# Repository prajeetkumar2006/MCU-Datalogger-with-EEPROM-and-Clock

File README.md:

# MCU-Datalogger-with-EEPROM-and-Clock
A custom-designed ATmega328P-based data logger PCB featuring dual I²C EEPROMs and a DS1337 real-time clock for reliable time-stamped data storage.

This project is a microcontroller-based data logger designed using KiCad. It uses an ATmega328P as the main controller, a DS1337 real-time clock for accurate timekeeping, and dual 24LC1025 EEPROMs for non-volatile data storage. The system logs sensor or system data with date and time information and provides I²C, UART, and ICSP interfaces for communication, programming, and debugging.

# Features
- Microcontroller: ATmega328P-AU (16 MHz)
- Real-time clock: DS1337S with 32.768 kHz crystal
- Non-volatile memory: 2 × 24LC1025 EEPROM (I²C)
- Connectivity: I²C header, UART (RX/TX) header, GPIO header, 6-pin ICSP
- Indicators: 2 status LEDs
- Power: Coin-cell Battery (BT1) for RTC backup
- Board: 2-layer PCB; 87.63 mm × 39.116 mm; 4 mounting holes
- KiCad version: 9.0.0

## Hardware Components

### Integrated Circuits (ICs)
- ATmega328P – Main microcontroller
- DS1337 – Real-Time Clock (RTC)
- 24LC1025 – I2C EEPROM (x2)

### Resistors (R)
- R1 – 330 Ω
- R2, R3 – 4.7 kΩ
- R4 – 10 kΩ

### Capacitors (C)
- C1, C2 – 22 pF
- C3, C4 – 100 nF
- C5 – 10 µF

### Crystals (X)
- X1 – 16 MHz
- X2 – 32.768 kHz

### Connectors / Jumpers (J)
- ICSP header – MCU programming
- UART header – Serial communication
- I2C header – External peripherals
- Power header – VCC and GND

## Schematic Design

## PCB Design
### 2-Layer

### 4-Layer Design

## 3-D Model(2 Layer)

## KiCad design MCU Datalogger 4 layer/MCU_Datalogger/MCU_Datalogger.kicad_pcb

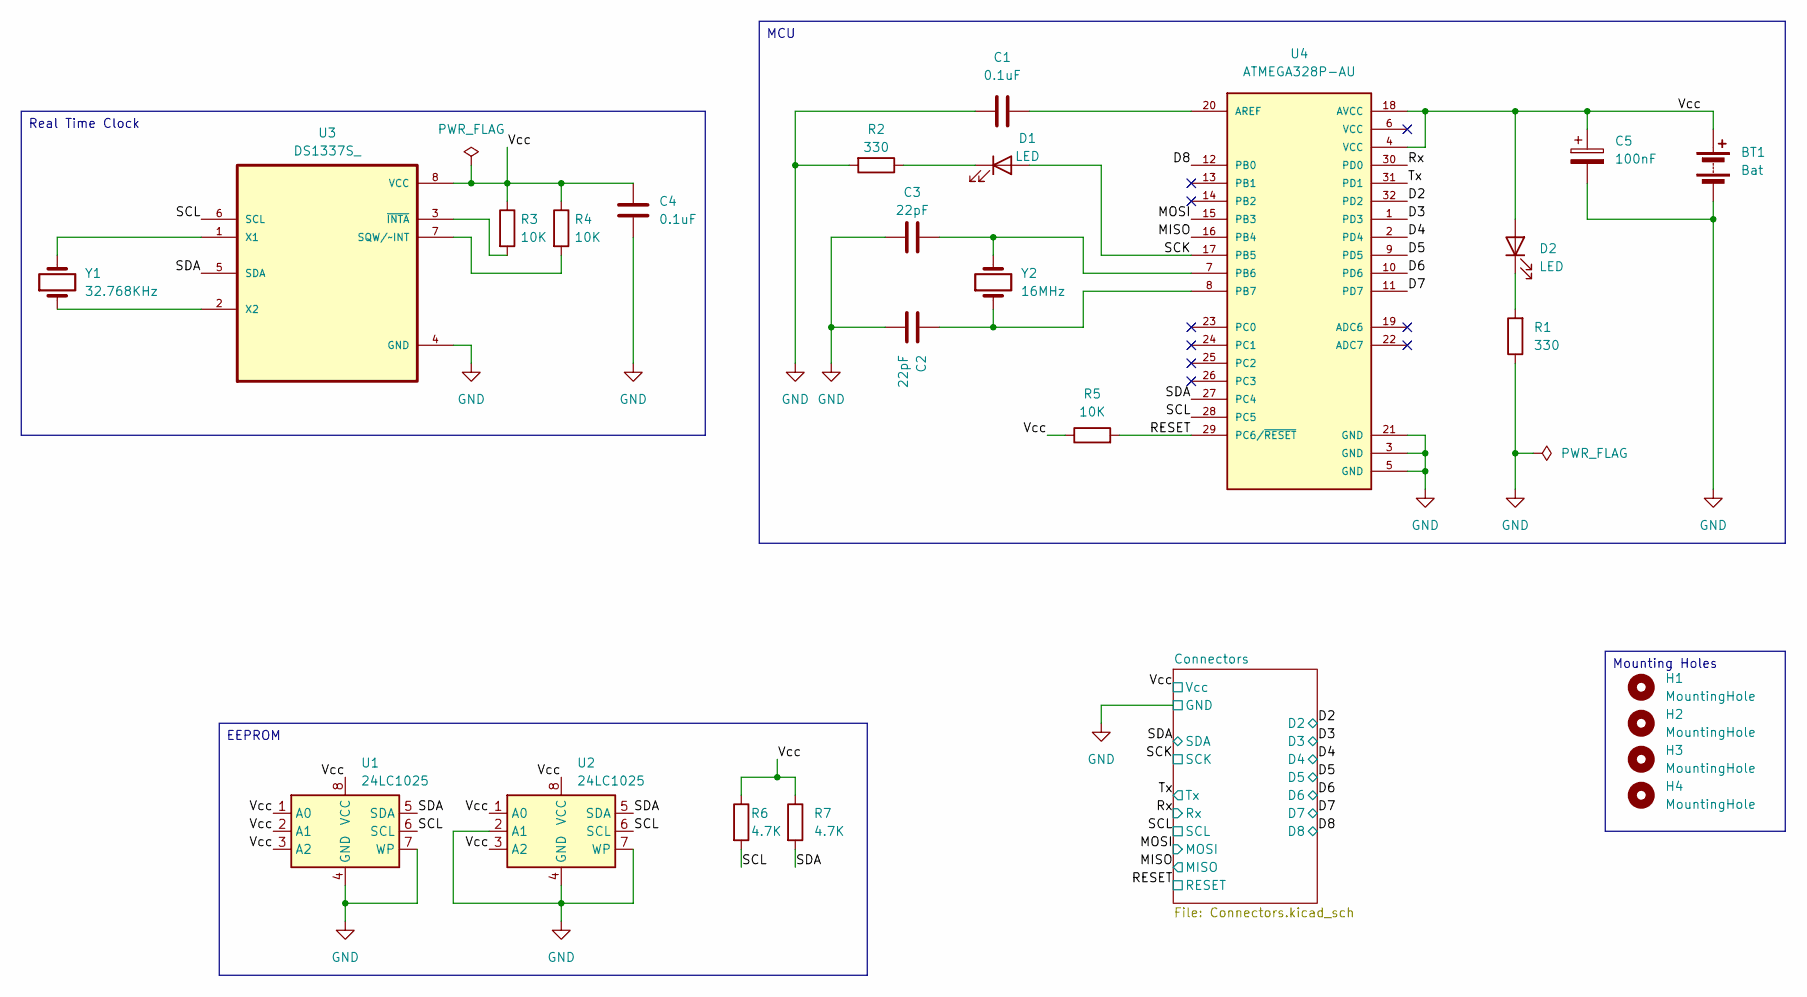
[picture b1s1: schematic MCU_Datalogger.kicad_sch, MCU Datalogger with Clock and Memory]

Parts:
BT1: Bat; PinHeader_1x02_P2.54mm_Vertical
C1, C4: 0.1uF; C_0805_2012Metric
C2, C3: 22pF; C_0805_2012Metric
C5: 100nF; C_0805_2012Metric
D1, D2: LED; LED_0805_2012Metric
H1, H2, H3, H4: MountingHole; MountingHole_2.1mm
R1, R2: 330; R_0805_2012Metric
R3, R4, R5: 10K; R_0805_2012Metric
R6, R7: 4.7K; R_0805_2012Metric
U1, U2: 24LC1025; SOIC-8_5.3x5.3mm_P1.27mm
U3: DS1337S_; SOIC127P600X175-8N
U4: ATMEGA328P-AU; QFP80P900X900X120-32N; PARTREV 8271A
Y1: 32.768KHz; Crystal_SMD_5032-2Pin_5.0x3.2mm_HandSoldering
Y2: 16MHz; Crystal_SMD_5032-2Pin_5.0x3.2mm_HandSoldering

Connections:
/D2: U4.32 (PD2); also elsewhere on the board
/D3: U4.1 (PD3); also elsewhere on the board
/D4: U4.2 (PD4); also elsewhere on the board
/D5: U4.9 (PD5); also elsewhere on the board
/D6: U4.10 (PD6); also elsewhere on the board
/D7: U4.11 (PD7); also elsewhere on the board
/D8: U4.12 (PB0); also elsewhere on the board
/MISO: U4.16 (PB4); also elsewhere on the board
/MOSI: U4.15 (PB3); also elsewhere on the board
/RESET: R5.2, U4.29 (PC6/~RESET); also elsewhere on the board
/Rx: U4.30 (PD0); also elsewhere on the board
/SCK: D1.2 (A), U4.17 (PB5); also elsewhere on the board
/SCL: R6.2, U1.6 (SCL), U2.6 (SCL), U3.6 (SCL), U4.28 (PC5); also elsewhere on the board
/SDA: R7.2, U1.5 (SDA), U2.5 (SDA), U3.5 (SDA), U4.27 (PC4); also elsewhere on the board
/Tx: U4.31 (PD1); also elsewhere on the board
/Vcc: BT1.1 (+), C4.1, C5.1, D2.2 (A), R3.1, R4.1, R5.1, R6.1, R7.1, U1.1 (A0), U1.2 (A1), U1.3 (A2), U1.8 (VCC), U2.1 (A0), U2.3 (A2), U2.8 (VCC), U3.8 (VCC), U4.4 (VCC), U4.18 (AVCC); also elsewhere on the board
GND: BT1.2 (-), C1.1, C2.2, C3.1, C4.2, C5.2, R1.1, R2.2, U1.4 (GND), U1.7 (WP), U2.2 (A1), U2.4 (GND), U2.7 (WP), U3.4 (GND), U4.3 (GND), U4.5 (GND), U4.21 (GND); also elsewhere on the board
unnamed: D1.1 (K), R2.1
unnamed: D2.1 (K), R1.2
unnamed: R4.2, U3.7 (SQW/~INT)
unnamed: U3.1 (X1), Y1.2
unnamed: U3.2 (X2), Y1.1
unnamed: R3.2, U3.3 (~INTA)
unnamed: C1.2, U4.20 (AREF)
unnamed: C3.2, U4.7 (PB6), Y2.2
unnamed: C2.1, U4.8 (PB7), Y2.1

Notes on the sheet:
Real Time Clock
Mounting Holes
MCU
EEPROM

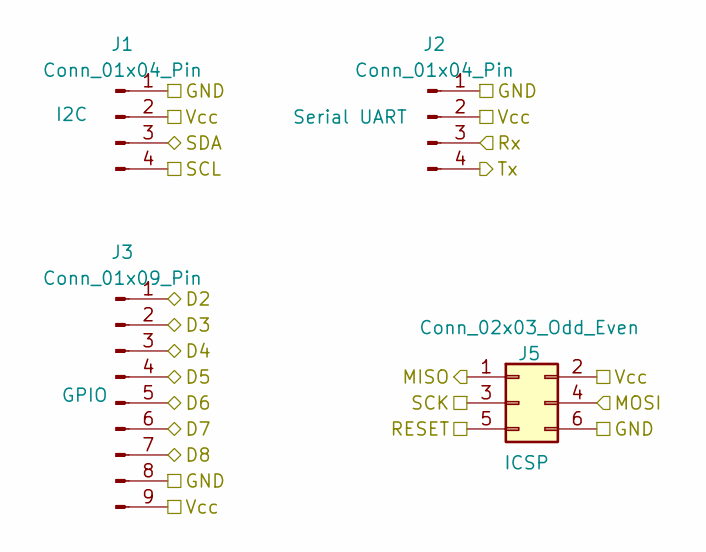
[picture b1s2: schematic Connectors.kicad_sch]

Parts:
J1, J2: Conn_01x04_Pin; PinHeader_1x04_P2.54mm_Vertical
J3: Conn_01x09_Pin; PinHeader_1x09_P2.54mm_Vertical
J5: Conn_02x03_Odd_Even; PinHeader_2x03_P2.54mm_Vertical

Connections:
/D2: J3.1; also elsewhere on the board
/D3: J3.2; also elsewhere on the board
/D4: J3.3; also elsewhere on the board
/D5: J3.4; also elsewhere on the board
/D6: J3.5; also elsewhere on the board
/D7: J3.6; also elsewhere on the board
/D8: J3.7; also elsewhere on the board
/MISO: J5.1; also elsewhere on the board
/MOSI: J5.4; also elsewhere on the board
/RESET: J5.5; also elsewhere on the board
/Rx: J2.3; also elsewhere on the board
/SCK: J5.3; also elsewhere on the board
/SCL: J1.4; also elsewhere on the board
/SDA: J1.3; also elsewhere on the board
/Tx: J2.4; also elsewhere on the board
/Vcc: J1.2, J2.2, J3.9, J5.2; also elsewhere on the board
GND: J1.1, J2.1, J3.8, J5.6; also elsewhere on the board

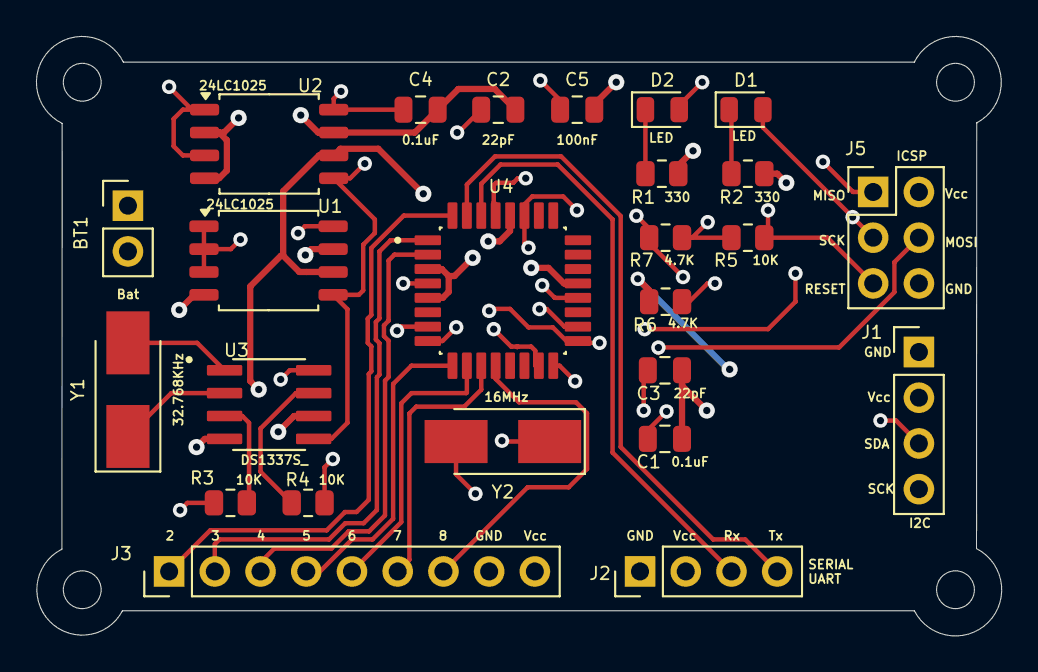
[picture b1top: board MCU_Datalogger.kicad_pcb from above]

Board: 4 copper layers, 53.6 x 33.3 mm, 29 parts (0 on the bottom side), 26 nets.

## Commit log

2025-12-29 Update README with project details and features
    Expanded project description and detailed hardware components.
